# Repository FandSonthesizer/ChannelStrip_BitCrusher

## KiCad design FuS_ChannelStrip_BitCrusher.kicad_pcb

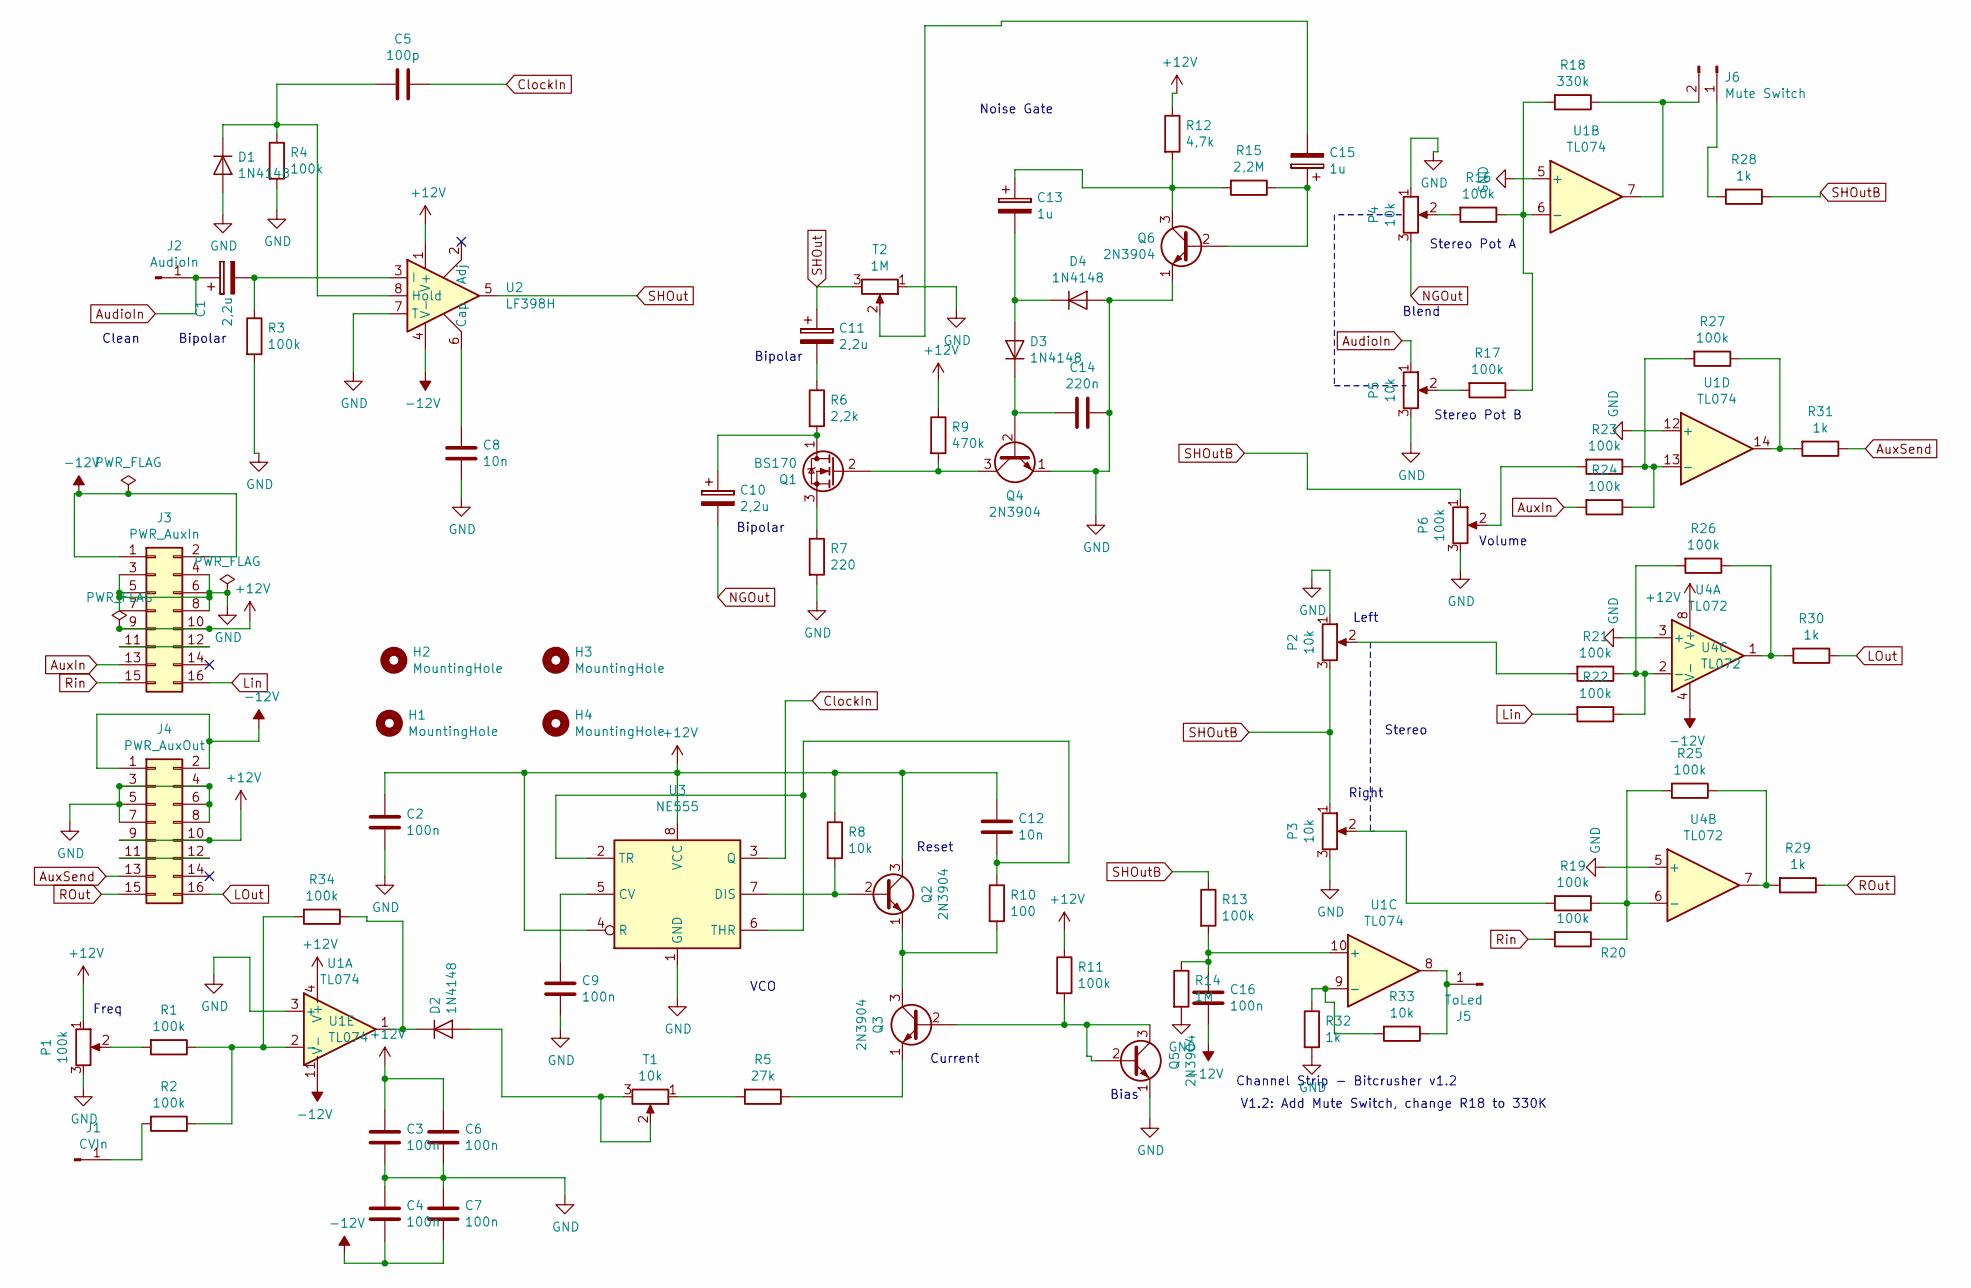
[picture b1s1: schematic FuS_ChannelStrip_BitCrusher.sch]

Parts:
C1, C10, C11: 2,2u; Elko_D6.3mm_P2.50mm
C2, C3, C4, C6, C7, C9, C16: 100n; Kondensator_Keramik
C5: 100p; Kondensator_Keramik
C8, C12: 10n; Kondensator_Keramik
C13, C15: 1u; Elko_D6.3mm_P2.50mm
C14: 220n; Kondensator_Keramik
D1, D2, D3, D4: 1N4148; Diode_Horizontal
H1, H2, H3, H4: MountingHole; MountHole
J1: CVIn; Stift
J2: AudioIn; Stift
J3: PWR_AuxIn; PinHeader_2x08_P2.54mm_Vertical
J4: PWR_AuxOut; PinHeader_2x08_P2.54mm_Vertical
J5: ToLed; Stift
J6: Mute Switch; Stift_x02
P1, P6: 100k; Trimmer_Vertical
P2, P3, P4, P5: 10k; Trimmer_Vertical
Q1: BS170; TO-92L_Wide
Q2, Q3, Q4, Q5, Q6: 2N3904; TO-92L_Wide
R1, R2, R3, R4, R11, R13, R16, R17, R19, R20, R21, R22, R23, R24, R25, R26, R27, R34: 100k; Widerstand_liegend
R5: 27k; Widerstand_liegend
R6: 2,2k; Widerstand_liegend
R7: 220; Widerstand_liegend
R8, R33: 10k; Widerstand_liegend
R9: 470k; Widerstand_liegend
R10: 100; Widerstand_liegend
R12: 4,7k; Widerstand_liegend
R14: 1M; Widerstand_liegend
R15: 2,2M; Widerstand_liegend
R18: 330k; Widerstand_liegend
R28, R29, R30, R31, R32: 1k; Widerstand_liegend
T1: 10k; Trimmer_Vertical
T2: 1M; Trimmer_Vertical
U1: TL074; DIP-14_W7.62mm_Socket_LongPads
U2: LF398H; DIP-8_W7.62mm_Socket_LongPads
U3: NE555; DIP-8_W7.62mm_Socket_LongPads
U4: TL072; DIP-8_W7.62mm_Socket_LongPads

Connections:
+12V: C2.1, C3.1, C6.1, C12.1, J3.9, J3.10, J4.9, J4.10, P1.1, Q2.3 (C), R8.1, R9.1, R11.1, R12.1, U1.4 (V+), U2.1 (V+), U3.4 (R), U3.8 (VCC), U4.8 (V+)
-12V: C4.2, C7.2, C16.2, J3.1, J3.2, J4.1, J4.2, U1.11 (V-), U2.4 (V-), U4.4 (V-)
AudioIn: C1.1, J2.1, P5.1
AuxIn: J3.13, R24.2
AuxSend: J4.13, R31.1
ClockIn: C5.1, U3.3 (Q)
GND: C2.2, C3.2, C4.1, C6.2, C7.1, C8.2, C9.2, C14.1, D1.2 (A), D4.2 (A), J3.3, J3.4, J3.5, J3.6, J3.7, J3.8, J4.3, J4.4, J4.5, J4.6, J4.7, J4.8, P1.3, P2.1, P3.3, P4.1, P5.3, P6.3, Q4.1 (E), Q5.1 (E), Q6.1 (E), R3.2, R4.2, R7.2, R14.2, R32.2, T2.1, U1.3 (+), U1.5 (+), U1.12 (+), U2.7 (T), U3.1 (GND), U4.3 (+), U4.5 (+)
LOut: J4.16, R30.1
Lin: J3.16, R22.2
NGOut: C10.2, P4.3
unnamed: C1.2, R3.1, U2.3 (I)
unnamed: C5.2, D1.1 (K), R4.1, U2.8 (Hold)
unnamed: C8.1, U2.6 (Cap)
unnamed: C9.1, U3.5 (CV)
unnamed: C10.1, Q1.1 (D), R6.2
unnamed: C11.2, R6.1
unnamed: C12.2, R10.1, U3.2 (TR), U3.6 (THR)
unnamed: C13.1, Q6.3 (C), R12.2, R15.2
unnamed: C13.2, D3.2 (A), D4.1 (K)
unnamed: C14.2, D3.1 (K), Q4.2 (B)
unnamed: C15.1, Q6.2 (B), R15.1
unnamed: C15.2, T2.2
unnamed: C16.1, R13.2, R14.1, U1.10 (+)
unnamed: D2.1 (K), R34.1, U1.1
unnamed: D2.2 (A), T1.2, T1.3
unnamed: J1.1, R2.2
unnamed: J3.11, J3.12
unnamed: J4.11, J4.12
unnamed: J5.1, R33.1, U1.8
unnamed: J6.1, R28.2
unnamed: J6.2, R18.1, U1.7
unnamed: P1.2, R1.2
unnamed: P2.2, R21.2
unnamed: P3.2, R19.2
unnamed: P4.2, R16.2
unnamed: P5.2, R17.2
unnamed: P6.2, R23.2
unnamed: Q1.2 (G), Q4.3 (C), R9.2
unnamed: Q1.3 (S), R7.1
unnamed: Q2.1 (E), Q3.3 (C), R10.2
unnamed: Q2.2 (B), R8.2, U3.7 (DIS)
unnamed: Q3.1 (E), R5.1
unnamed: Q3.2 (B), Q5.2 (B), Q5.3 (C), R11.2
unnamed: R1.1, R2.1, R34.2, U1.2 (-)
unnamed: R5.2, T1.1
unnamed: R16.1, R17.1, R18.2, U1.6 (-)
unnamed: R19.1, R20.1, R25.2, U4.6 (-)
unnamed: R21.1, R22.1, R26.2, U4.2 (-)
unnamed: R23.1, R24.1, R27.2, U1.13 (-)
unnamed: R25.1, R29.2, U4.7
unnamed: R26.1, R30.2, U4.1
unnamed: R27.1, R31.2, U1.14
unnamed: R32.1, R33.2, U1.9 (-)
ROut: J4.15, R29.1
Rin: J3.15, R20.2
SHOut: C11.1, T2.3, U2.5
SHOutB: P2.3, P3.1, P6.1, R13.1, R28.1

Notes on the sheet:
VCO
Bias
Current
Reset
Freq
Channel Strip - Bitcrusher v1.2
Stereo Pot A
Stereo Pot B
Blend
Bipolar
Volume
Left
Right
Noise Gate
Clean
Stereo
V1.2: Add Mute Switch, change R18 to 330K

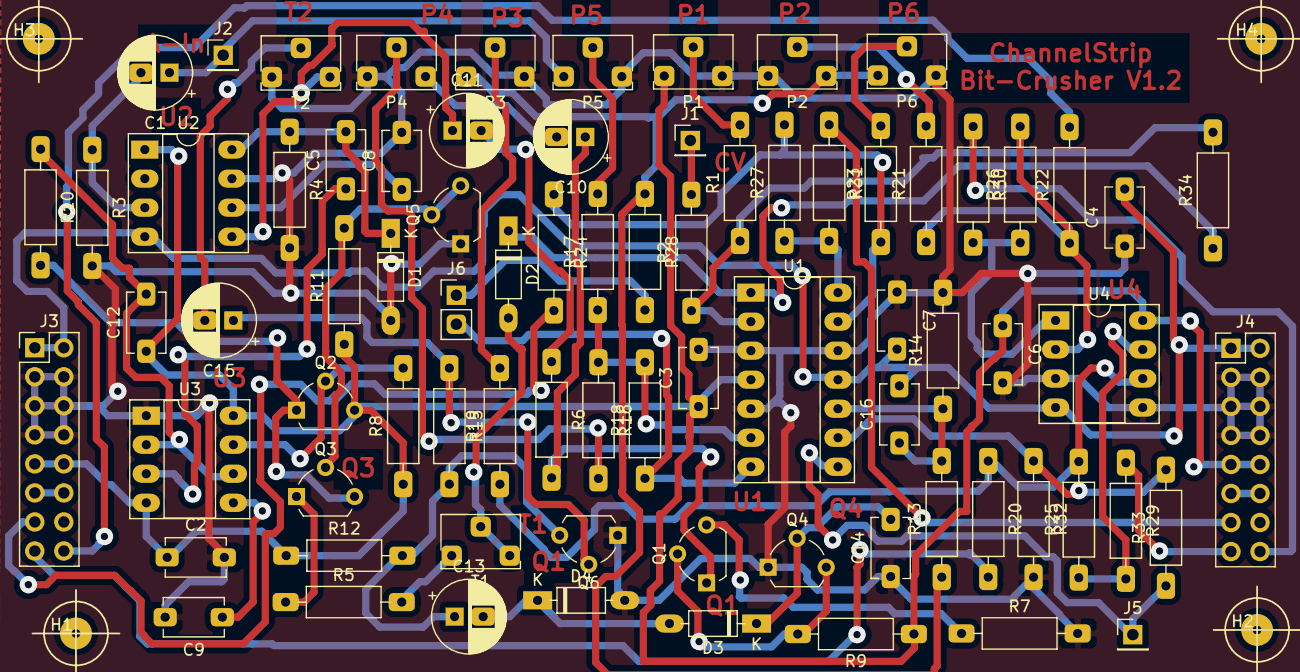
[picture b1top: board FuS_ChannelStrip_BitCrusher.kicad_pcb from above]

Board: 2 copper layers, 82 parts (0 on the bottom side), 57 nets.
